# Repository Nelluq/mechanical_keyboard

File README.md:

# Mechanical Keyboard

## Background and Overview
This is a simple exposed-PCB design for a Cherry MX-based mechanical keyboard. It is a full-size 104-key board, but also
includes 4 extra keys that can be used for anything. It uses PCB-mount Cherry MX switches, and can be assembled with any
color non-backlit switch (I don't care for keyboard backlighting, so I didn't include it). It runs on an STM32F070C6
microcontroller.

The PCB was designed in [KiCad](https://kicad-pcb.org), which conveniently already had Cherry MX key switches in its
component libraries. Except for the key switches and the USB port, all the components are surface mount. This can make
it a little trickier to hand solder for people with less soldering experience (especially the 108 SOD-323 diodes...),
but it's entirely possible.

I started the project in August 2019 because I needed a better keyboard for work. I also wanted to try out STM32 MCUs,
which I hadn't used before. I couldn't get the firmware working initially, so set it aside for a few months and finally
finished it in February 2020. The first version of the firmware was written using the STM32Cube framework with
STM32 HAL, but I ended up not being satisfied with the generated code from that system, and the keyboard itself wasn't
working as well as I wanted. Eventually, in April 2020, I rewrote the entirity of the firmware using
[libopencm3](https://gitub.com/libopencm3/libopencm3), which is vastly cleaner and nicer to work with than ST's own
framework.

## Example

This is my keyboard, built on the Rev 2 PCB (newer PCB versions are slightly improved, but generally the same). I used
Cherry MX brown switches (I prefer blues, but I wanted this to be quieter for work) and opted for matte black
soldermask, which I think looks awesome.

## Instructions
Coming soon

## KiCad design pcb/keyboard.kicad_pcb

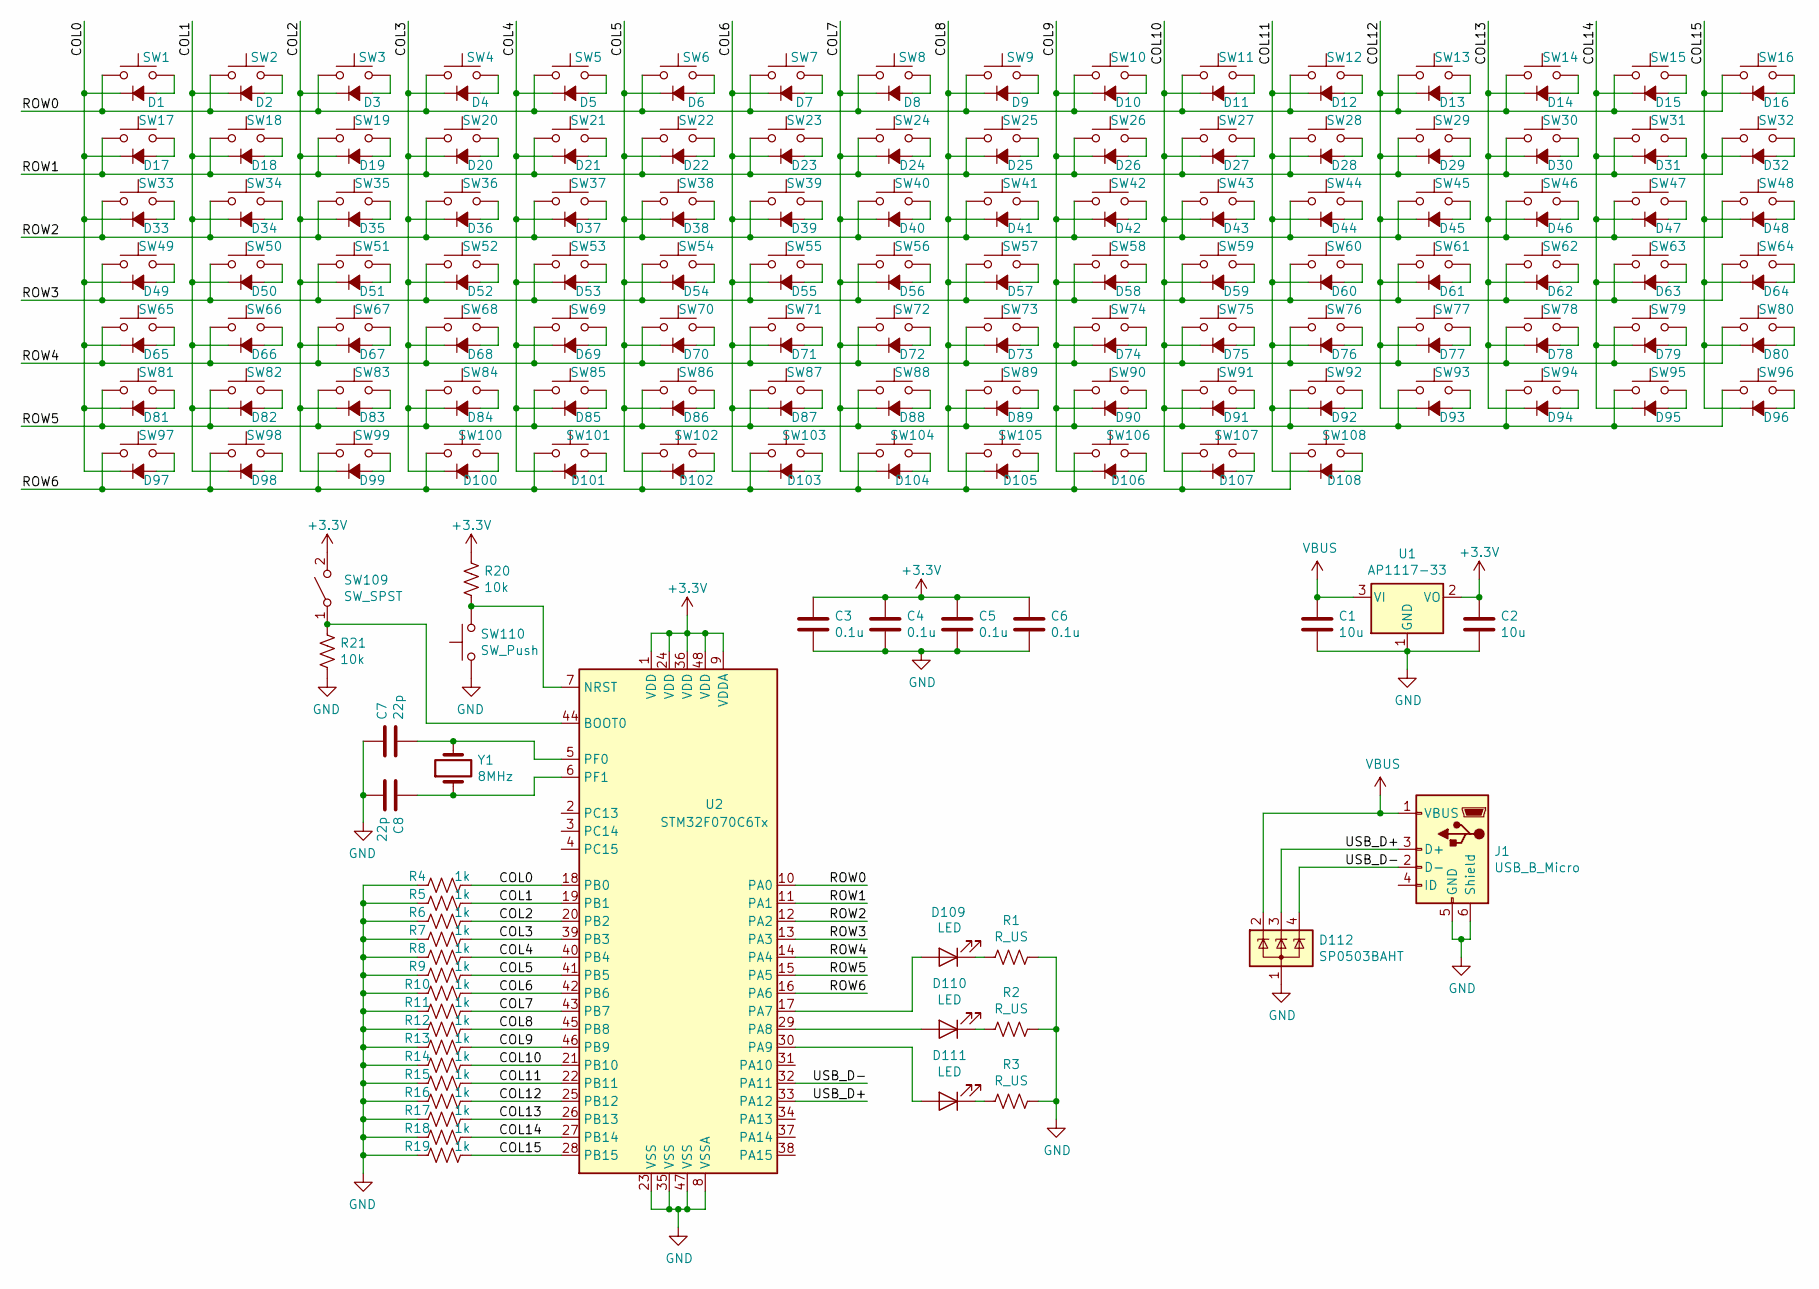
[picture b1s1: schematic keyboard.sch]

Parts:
C1, C2: 10u; C_0603_1608Metric
C3, C4, C5, C6: 0.1u; C_0603_1608Metric
C7, C8: 22p; C_0603_1608Metric
D1, D2, D3, D4, D5, D6, D7, D8, D9, D10, D11, D12, D13, D14, D15, D16, D17, D18, D19, D20, D21, D22, D23, D24, D25, D26, D27, D28, D29, D30, D31, D32, D33, D34, D35, D36, D37, D38, D39, D40, D41, D42, D43, D44, D45, D46, D47, D48, D49, D50, D51, D52, D53, D54, D55, D56, D57, D58, D59, D60, D61, D62, D63, D64, D65, D66, D67, D68, D69, D70, D71, D72, D73, D74, D75, D76, D77, D78, D79, D80, D81, D82, D83, D84, D85, D86, D87, D88, D89, D90, D91, D92, D93, D94, D95, D96, D97, D98, D99, D100, D101, D102, D103, D104, D105, D106, D107, D108: D_Small_ALT; D_0603_1608Metric
D109, D110, D111: LED; LED_0603_1608Metric
D112: SP0503BAHT; SOT-143
J1: USB_B_Micro; USB_Micro-B_Amphenol_10103594-0001LF_Horizontal
R1, R2, R3: R_US; R_0603_1608Metric
R4, R5, R6, R7, R8, R9, R10, R11, R12, R13, R14, R15, R16, R17, R18, R19: 1k; R_0603_1608Metric
R20, R21: 10k; R_0603_1608Metric
SW1, SW2, SW3, SW4, SW5, SW6, SW7, SW8, SW9, SW10, SW11, SW12, SW13, SW15, SW16, SW18, SW19, SW20, SW21, SW22, SW23, SW24, SW25, SW26, SW27, SW28, SW29, SW31, SW32, SW34, SW35, SW36, SW37, SW38, SW39, SW40, SW41, SW42, SW43, SW44, SW46, SW47, SW48, SW50, SW51, SW52, SW53, SW54, SW55, SW56, SW57, SW58, SW59, SW61, SW62, SW63, SW64, SW73, SW74, SW75, SW76, SW77, SW78, SW79, SW80, SW81, SW82, SW83, SW84, SW85, SW86, SW87, SW89, SW90, SW91, SW92, SW93, SW94, SW97, SW98, SW99, SW100, SW101, SW102, SW103, SW104, SW105, SW106, SW107, SW108: SW_Push; SW_Cherry_MX_1.00u_PCB
SW14, SW96: SW_Push; SW_Cherry_MX_2.00u_PCB
SW17, SW30: SW_Push; SW_Cherry_MX_1.50u_PCB
SW33: SW_Push; SW_Cherry_MX_1.75u_PCB
SW45, SW49: SW_Push; SW_Cherry_MX_2.25u_PCB
SW60: SW_Push; SW_Cherry_MX_2.75u_PCB
SW65, SW66, SW67, SW69, SW70, SW71, SW72: SW_Push; SW_Cherry_MX_1.25u_PCB
SW68: SW_Push; SW_Cherry_MX_6.25u_PCB
SW88, SW95: SW_Push; SW_Cherry_MX_2.00u_Vertical_PCB
SW109: SW_SPST; SW_SPST_PTS645
SW110: SW_Push; SW_SPST_PTS645
U1: AP1117-33; SOT-223-3_TabPin2
U2: STM32F070C6Tx; LQFP-48_7x7mm_P0.5mm
Y1: 8MHz; Crystal_SMD_HC49-SD

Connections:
+3V3: C2.1, C3.1, C4.1, C5.1, C6.1, R20.1, SW109.2 (B), U1.2 (VO), U2.1 (VDD), U2.9 (VDDA), U2.24 (VDD), U2.36 (VDD), U2.48 (VDD)
/COL0: D1.1 (K), D17.1 (K), D33.1 (K), D49.1 (K), D65.1 (K), D81.1 (K), D97.1 (K), R4.1, U2.18 (PB0)
/COL1: D2.1 (K), D18.1 (K), D34.1 (K), D50.1 (K), D66.1 (K), D82.1 (K), D98.1 (K), R5.1, U2.19 (PB1)
/COL2: D3.1 (K), D19.1 (K), D35.1 (K), D51.1 (K), D67.1 (K), D83.1 (K), D99.1 (K), R6.1, U2.20 (PB2)
/COL3: D4.1 (K), D20.1 (K), D36.1 (K), D52.1 (K), D68.1 (K), D84.1 (K), D100.1 (K), R7.1, U2.39 (PB3)
/COL4: D5.1 (K), D21.1 (K), D37.1 (K), D53.1 (K), D69.1 (K), D85.1 (K), D101.1 (K), R8.1, U2.40 (PB4)
/COL5: D6.1 (K), D22.1 (K), D38.1 (K), D54.1 (K), D70.1 (K), D86.1 (K), D102.1 (K), R9.1, U2.41 (PB5)
/COL6: D7.1 (K), D23.1 (K), D39.1 (K), D55.1 (K), D71.1 (K), D87.1 (K), D103.1 (K), R10.1, U2.42 (PB6)
/COL7: D8.1 (K), D24.1 (K), D40.1 (K), D56.1 (K), D72.1 (K), D88.1 (K), D104.1 (K), R11.1, U2.43 (PB7)
/COL8: D9.1 (K), D25.1 (K), D41.1 (K), D57.1 (K), D73.1 (K), D89.1 (K), D105.1 (K), R12.1, U2.45 (PB8)
/COL9: D10.1 (K), D26.1 (K), D42.1 (K), D58.1 (K), D74.1 (K), D90.1 (K), D106.1 (K), R13.1, U2.46 (PB9)
/COL10: D11.1 (K), D27.1 (K), D43.1 (K), D59.1 (K), D75.1 (K), D91.1 (K), D107.1 (K), R14.1, U2.21 (PB10)
/COL11: D12.1 (K), D28.1 (K), D44.1 (K), D60.1 (K), D76.1 (K), D92.1 (K), D108.1 (K), R15.1, U2.22 (PB11)
/COL12: D13.1 (K), D29.1 (K), D45.1 (K), D61.1 (K), D77.1 (K), D93.1 (K), R16.1, U2.25 (PB12)
/COL13: D14.1 (K), D30.1 (K), D46.1 (K), D62.1 (K), D78.1 (K), D94.1 (K), R17.1, U2.26 (PB13)
/COL14: D15.1 (K), D31.1 (K), D47.1 (K), D63.1 (K), D79.1 (K), D95.1 (K), R18.1, U2.27 (PB14)
/COL15: D16.1 (K), D32.1 (K), D48.1 (K), D64.1 (K), D80.1 (K), D96.1 (K), R19.1, U2.28 (PB15)
/ROW0: SW1.1, SW2.1, SW3.1, SW4.1, SW5.1, SW6.1, SW7.1, SW8.1, SW9.1, SW10.1, SW11.1, SW12.1, SW13.1, SW14.1, SW15.1, SW16.1, U2.10 (PA0)
/ROW1: SW17.1, SW18.1, SW19.1, SW20.1, SW21.1, SW22.1, SW23.1, SW24.1, SW25.1, SW26.1, SW27.1, SW28.1, SW29.1, SW30.1, SW31.1, SW32.1, U2.11 (PA1)
/ROW2: SW33.1, SW34.1, SW35.1, SW36.1, SW37.1, SW38.1, SW39.1, SW40.1, SW41.1, SW42.1, SW43.1, SW44.1, SW45.1, SW46.1, SW47.1, SW48.1, U2.12 (PA2)
/ROW3: SW49.1, SW50.1, SW51.1, SW52.1, SW53.1, SW54.1, SW55.1, SW56.1, SW57.1, SW58.1, SW59.1, SW60.1, SW61.1, SW62.1, SW63.1, SW64.1, U2.13 (PA3)
/ROW4: SW65.1, SW66.1, SW67.1, SW68.1, SW69.1, SW70.1, SW71.1, SW72.1, SW73.1, SW74.1, SW75.1, SW76.1, SW77.1, SW78.1, SW79.1, SW80.1, U2.14 (PA4)
/ROW5: SW81.1, SW82.1, SW83.1, SW84.1, SW85.1, SW86.1, SW87.1, SW88.1, SW89.1, SW90.1, SW91.1, SW92.1, SW93.1, SW94.1, SW95.1, SW96.1, U2.15 (PA5)
/ROW6: SW97.1, SW98.1, SW99.1, SW100.1, SW101.1, SW102.1, SW103.1, SW104.1, SW105.1, SW106.1, SW107.1, SW108.1, U2.16 (PA6)
/USB_D+: D112.3 (K), J1.3 (D+), U2.33 (PA12)
/USB_D-: D112.4 (K), J1.2 (D-), U2.32 (PA11)
GND: C1.2, C2.2, C3.2, C4.2, C5.2, C6.2, C7.1, C8.2, D112.1 (A), J1.5 (GND), J1.6 (Shield), R1.1, R2.1, R3.1, R4.2, R5.2, R6.2, R7.2, R8.2, R9.2, R10.2, R11.2, R12.2, R13.2, R14.2, R15.2, R16.2, R17.2, R18.2, R19.2, R21.2, SW110.2, U1.1 (GND), U2.8 (VSSA), U2.23 (VSS), U2.35 (VSS), U2.47 (VSS)
unnamed: C7.2, U2.5 (PF0), Y1.2
unnamed: C8.1, U2.6 (PF1), Y1.1
unnamed: D1.2 (A), SW1.2
unnamed: D2.2 (A), SW2.2
unnamed: D3.2 (A), SW3.2
unnamed: D4.2 (A), SW4.2
unnamed: D5.2 (A), SW5.2
unnamed: D6.2 (A), SW6.2
unnamed: D7.2 (A), SW7.2
unnamed: D8.2 (A), SW8.2
unnamed: D9.2 (A), SW9.2
unnamed: D10.2 (A), SW10.2
unnamed: D11.2 (A), SW11.2
unnamed: D12.2 (A), SW12.2
unnamed: D13.2 (A), SW13.2
unnamed: D14.2 (A), SW14.2
unnamed: D15.2 (A), SW15.2
unnamed: D16.2 (A), SW16.2
unnamed: D17.2 (A), SW17.2
unnamed: D18.2 (A), SW18.2
unnamed: D19.2 (A), SW19.2
unnamed: D20.2 (A), SW20.2
unnamed: D21.2 (A), SW21.2
unnamed: D22.2 (A), SW22.2
unnamed: D23.2 (A), SW23.2
unnamed: D24.2 (A), SW24.2
unnamed: D25.2 (A), SW25.2
unnamed: D26.2 (A), SW26.2
unnamed: D27.2 (A), SW27.2
unnamed: D28.2 (A), SW28.2
unnamed: D29.2 (A), SW29.2
unnamed: D30.2 (A), SW30.2
unnamed: D31.2 (A), SW31.2
unnamed: D32.2 (A), SW32.2
unnamed: D33.2 (A), SW33.2
unnamed: D34.2 (A), SW34.2
unnamed: D35.2 (A), SW35.2
unnamed: D36.2 (A), SW36.2
unnamed: D37.2 (A), SW37.2
unnamed: D38.2 (A), SW38.2
unnamed: D39.2 (A), SW39.2
unnamed: D40.2 (A), SW40.2
unnamed: D41.2 (A), SW41.2
unnamed: D42.2 (A), SW42.2
unnamed: D43.2 (A), SW43.2
unnamed: D44.2 (A), SW44.2
unnamed: D45.2 (A), SW45.2
unnamed: D46.2 (A), SW46.2
unnamed: D47.2 (A), SW47.2
unnamed: D48.2 (A), SW48.2
unnamed: D49.2 (A), SW49.2
unnamed: D50.2 (A), SW50.2
unnamed: D51.2 (A), SW51.2
unnamed: D52.2 (A), SW52.2
unnamed: D53.2 (A), SW53.2
unnamed: D54.2 (A), SW54.2
unnamed: D55.2 (A), SW55.2
unnamed: D56.2 (A), SW56.2
unnamed: D57.2 (A), SW57.2
unnamed: D58.2 (A), SW58.2
unnamed: D59.2 (A), SW59.2
unnamed: D60.2 (A), SW60.2
unnamed: D61.2 (A), SW61.2
unnamed: D62.2 (A), SW62.2
unnamed: D63.2 (A), SW63.2
unnamed: D64.2 (A), SW64.2
unnamed: D65.2 (A), SW65.2
unnamed: D66.2 (A), SW66.2
unnamed: D67.2 (A), SW67.2
unnamed: D68.2 (A), SW68.2
unnamed: D69.2 (A), SW69.2
unnamed: D70.2 (A), SW70.2
unnamed: D71.2 (A), SW71.2
unnamed: D72.2 (A), SW72.2
unnamed: D73.2 (A), SW73.2
unnamed: D74.2 (A), SW74.2
unnamed: D75.2 (A), SW75.2
unnamed: D76.2 (A), SW76.2
unnamed: D77.2 (A), SW77.2
unnamed: D78.2 (A), SW78.2
unnamed: D79.2 (A), SW79.2
unnamed: D80.2 (A), SW80.2
unnamed: D81.2 (A), SW81.2
unnamed: D82.2 (A), SW82.2
unnamed: D83.2 (A), SW83.2
unnamed: D84.2 (A), SW84.2
unnamed: D85.2 (A), SW85.2
unnamed: D86.2 (A), SW86.2
unnamed: D87.2 (A), SW87.2
unnamed: D88.2 (A), SW88.2
unnamed: D89.2 (A), SW89.2
unnamed: D90.2 (A), SW90.2
unnamed: D91.2 (A), SW91.2
unnamed: D92.2 (A), SW92.2
unnamed: D93.2 (A), SW93.2
unnamed: D94.2 (A), SW94.2
unnamed: D95.2 (A), SW95.2
unnamed: D96.2 (A), SW96.2
unnamed: D97.2 (A), SW97.2
unnamed: D98.2 (A), SW98.2
unnamed: D99.2 (A), SW99.2
unnamed: D100.2 (A), SW100.2
unnamed: D101.2 (A), SW101.2
unnamed: D102.2 (A), SW102.2
unnamed: D103.2 (A), SW103.2
unnamed: D104.2 (A), SW104.2
unnamed: D105.2 (A), SW105.2
unnamed: D106.2 (A), SW106.2
unnamed: D107.2 (A), SW107.2
unnamed: D108.2 (A), SW108.2
unnamed: D109.1 (K), R1.2
unnamed: D109.2 (A), U2.17 (PA7)
unnamed: D110.1 (K), R2.2
unnamed: D110.2 (A), U2.29 (PA8)
unnamed: D111.1 (K), R3.2
unnamed: D111.2 (A), U2.30 (PA9)
unnamed: R20.2, SW110.1, U2.7 (NRST)
unnamed: R21.1, SW109.1 (A), U2.44 (BOOT0)
VBUS: C1.1, D112.2 (K), J1.1 (VBUS), U1.3 (VI)

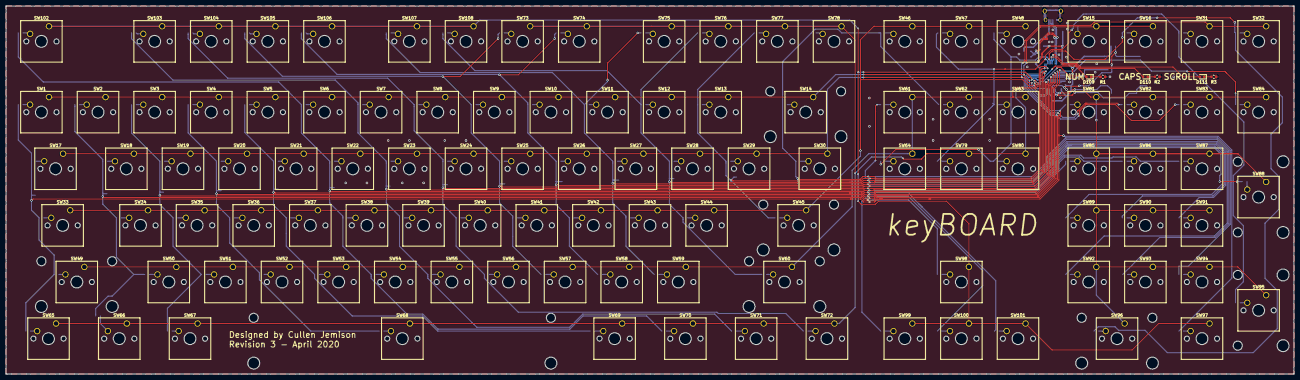
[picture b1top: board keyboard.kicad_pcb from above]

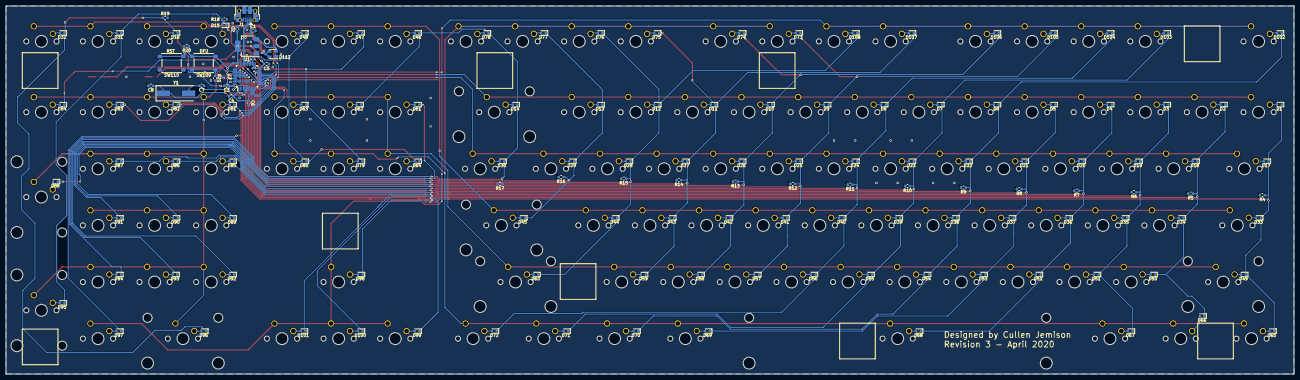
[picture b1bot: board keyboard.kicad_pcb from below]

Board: 2 copper layers, 433.4 x 123.8 mm, 255 parts (141 on the bottom side), 146 nets.

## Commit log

2020-04-22 Added libopencm3
2020-05-02 Added PCB
2020-05-02 Added firmware
2020-05-02 [#4] Halved polling speed
2020-05-02 Added initial readme and pictures
2020-05-02 Added more to readme
2020-05-03 Updated flash makefile rule and added vscode tasks
2020-05-03 [#3] Added rollover logic
2020-05-03 Added license
2020-05-03 Fixed indents
2020-05-03 [#1] Added support for LED lock status indicators
2020-05-03 [#2] Added ability to load macros from flash
2020-05-05 [#2] Allow setting macro codes by writing to HID endpoint
2020-05-05 [#2] Set the correct flag when reading macro config
2020-05-19 Increased polling rate, removed macro configurability via usb
2020-05-19 Added new keyboard image
2020-12-25 Moved C firmware to firmware_c
2020-12-25 Updated libopencm3 path
